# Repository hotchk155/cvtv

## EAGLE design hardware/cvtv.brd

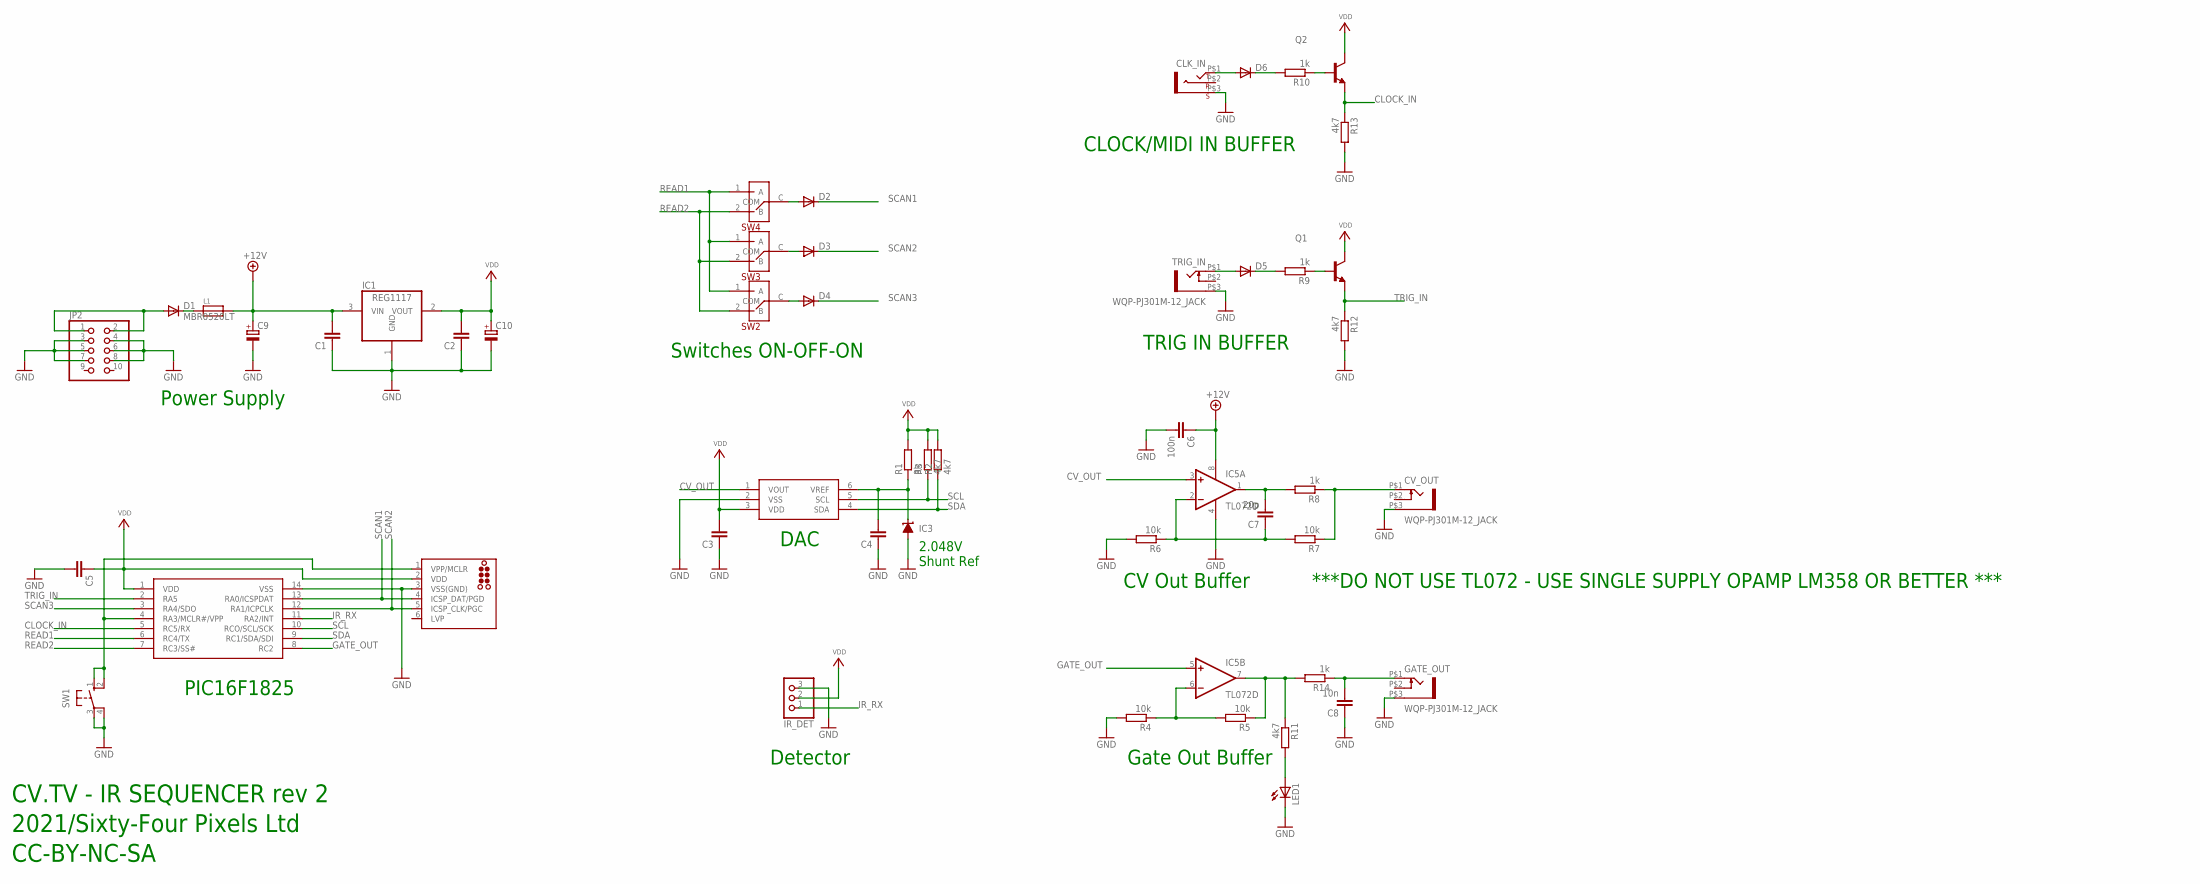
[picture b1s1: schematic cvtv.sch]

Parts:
C1, C2, C3, C4, C5: C-EUC0805; C0805
C6: 100n; C0805
C7: 20p; C0805
C8: 10n; C0805
C9, C10: CPOL-EUE2-5; E2-5
CLK_IN: THONKICONN_STEREO; WQP-PJ301M-ST
CV_OUT: WQP-PJ301M-12_JACK
D1: MBR0520LT; SOD123
D2, D3, D4, D5, D6: TS4148; D0805
GATE_OUT: WQP-PJ301M-12_JACK
IC1: REG1117; SOT223
IC2: PIC16F1825SO14; SO14
IC3: LM4041A12DBZ; DBZ_R-PDSO-G3
IC4: MCP4726; SOT23-6
IC5: TL072D; SO08
ICSP: TC2030-MCP-NL
IR_DET: PINHD-1X3; 1X03
JP2: PINHD-2X5; 2X05
L1: FERRITE; 0603
LED1: LED3MM
Q1, Q2: MMBT3904LT1-NPN-SOT23-BEC; SOT23-BEC
R1: 3k; R0805
R2, R3, R11, R12, R13: 4k7; R0805
R4, R5, R6, R7: 10k; R0805
R8, R9, R10, R14: 1k; R0805
SW1: 10-XX; B3F-10XX
SW2, SW3, SW4: MICRO-SPDT
TRIG_IN: WQP-PJ301M-12_JACK

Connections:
+12V: C1.2, C6.1, C9.+, IC1.3 (VIN), IC5.8 (V+), L1.2
CLOCK_IN: IC2.5 (RC5/RX), Q2.E, R13.1
CV_OUT: IC4.1 (VOUT), IC5.3 (+IN)
GATE_OUT: IC2.8 (RC2), IC5.5 (+IN)
GND: C1.1, C2.1, C3.1, C4.1, C5.2, C6.2, C8.1, C9.-, C10.-, CLK_IN.P$3 (S), CV_OUT.P$3 (1), GATE_OUT.P$3 (1), IC1.1 (GND), IC2.14 (VSS), IC3.2 (A), IC4.2 (VSS), IC5.4 (V-), ICSP.3 (VSS(GND)), IR_DET.3, JP2.3, JP2.4, JP2.5, JP2.6, JP2.7, JP2.8, LED1.K (C), R4.2, R6.2, R12.2, R13.2, SW1.3, SW1.4 (P1), TRIG_IN.P$3 (1)
IR_RX: IC2.11 (RA2/INT), IR_DET.1
unnamed: D1.A, JP2.1, JP2.2
unnamed: IC2.4 (RA3/MCLR#/VPP), ICSP.1 (VPP/MCLR), SW1.1 (S), SW1.2 (S1)
unnamed: CLK_IN.P$1 (T), D6.A
unnamed: D1.C, L1.1
unnamed: LED1.A, R11.2
unnamed: C4.2, IC3.1 (C), IC4.6 (VREF), R1.1
unnamed: D6.K (C), R10.2
unnamed: Q2.B, R10.1
unnamed: D5.A, TRIG_IN.P$1 (2)
unnamed: D2.A, SW4.C (COM)
unnamed: D5.K (C), R9.2
unnamed: IC5.7 (OUT), R5.1, R11.1, R14.2
unnamed: D3.A, SW3.C (COM)
unnamed: C8.2, GATE_OUT.P$1 (2), R14.1
unnamed: IC5.6 (-IN), R4.1, R5.2
unnamed: C7.1, IC5.2 (-IN), R6.1, R7.2
unnamed: CV_OUT.P$1 (2), R7.1, R8.1
unnamed: C7.2, IC5.1 (OUT), R8.2
unnamed: Q1.B, R9.1
unnamed: D4.A, SW2.C (COM)
READ1: IC2.6 (RC4/TX), SW2.1 (A), SW3.1 (A), SW4.1 (A)
READ2: IC2.7 (RC3/SS#), SW2.2 (B), SW3.2 (B), SW4.2 (B)
SCAN1: D2.K (C), IC2.13 (RA0/ICSPDAT), ICSP.4 (ICSP_DAT/PGD)
SCAN2: D3.K (C), IC2.12 (RA1/ICPCLK), ICSP.5 (ICSP_CLK/PGC)
SCAN3: D4.K (C), IC2.3 (RA4/SDO)
SCL: IC2.10 (RCO/SCL/SCK), IC4.5 (SCL), R3.1
SDA: IC2.9 (RC1/SDA/SDI), IC4.4 (SDA), R2.1
TRIG_IN: IC2.2 (RA5), Q1.E, R12.1
VDD: C2.2, C3.2, C5.1, C10.+, IC1.2 (VOUT), IC2.1 (VDD), IC4.3 (VDD), ICSP.2 (VDD), IR_DET.2, Q1.C, Q2.C, R1.2, R2.2, R3.2

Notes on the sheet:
DAC
2.048V Shunt Ref
Power Supply
Detector
PIC16F1825
Switches ON-OFF-ON
CV Out Buffer
Gate Out Buffer
CV.TV - IR SEQUENCER rev 2
2021/Sixty-Four Pixels Ltd
CC-BY-NC-SA
***DO NOT USE TL072 - USE SINGLE SUPPLY OPAMP LM358 OR BETTER ***
CLOCK/MIDI IN BUFFER
TRIG IN BUFFER

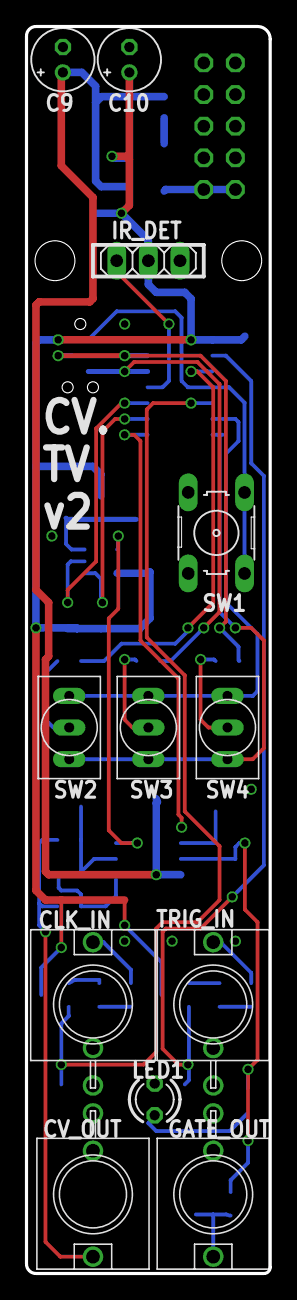
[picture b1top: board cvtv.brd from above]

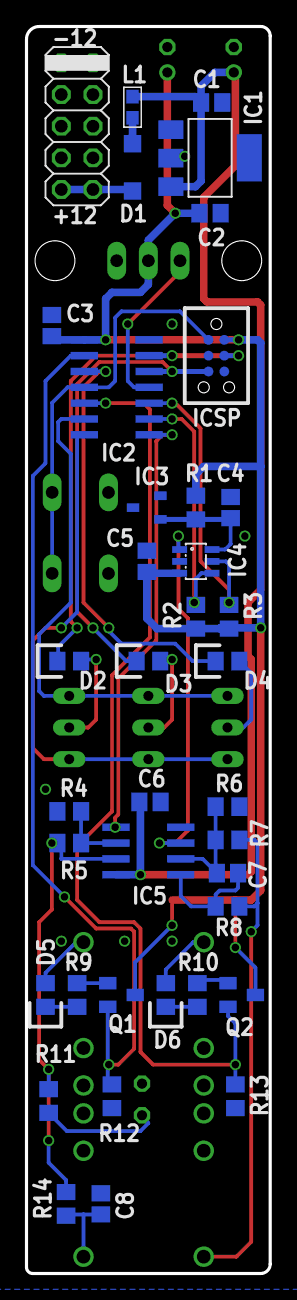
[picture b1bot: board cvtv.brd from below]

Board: 2 copper layers, 19.6 x 100.1 mm, 50 parts (38 on the bottom side), 35 nets.

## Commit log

2020-11-24 rfsw
2021-12-08 asdsa
2021-12-09 sdfdfsdfs
2021-12-23 board updates
2022-01-15 rename
2025-04-09 check in updates

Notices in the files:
parts and their libraries:
tag-connect: ©2009 ROFA.cz - modified and updated by Robert Darlington ‹rdarlington@gmail.com›
